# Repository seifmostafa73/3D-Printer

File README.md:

# 3D-Printer

this is a SKR-inspired 3D printer baord 

# Technical information
v1.1
* ### LPC1769 : 120 MHZ Cortex®-M3 Mc 
include 512 kB of flash memory, 64 kB of data memory, Ethernet MAC, USB Device/Host/OTG, 8-channel DMA controller, 4 UARTs, 2 CAN channels, 3 SSP/SPI, 3 I2C, I2S, 8-channel 12-bit ADC, 10-bit DAC, motor control PWM, Quadrature Encoder interface, 4 general purpose timers, 6-output general purpose PWM, ultra-low power Real-Time Clock with separate battery supply, and up to 70 general purpose I/O pins. The LPC1769 is pin-compatible to the 100-pin LPC2368 Arm7™ MCU 

* ### Integrated Buck-Converted - 5V output
* ### Integrated 15A heat-bed MOSFET controller
* ### 2 Controlled Fans
* ### 4 integrated TMC5160 Circuits [the circuit is desinged to be easily repolaced in case of any failure.]
* ### on-Board ESP32 for wifi support
* ### USB Port
* ### 3-Axis end stops 
* ### 3 Analog pins ready for extensions
* ### SPI pins for programming 
* ### Seperate GND, AGND planes
* ### replacable power fuses
* ### calculated Singal integrity [Cross-talk , Power Dissipation , Diffrential pairs ,Current and voltage limits , Protetion cirucits ]

# 3D preview
https://a360.co/3tKiZm6

# ScreenShots

[Motherboard V1.1.pdf](https://github.com/seifmostafa73/3D-Printer/files/8233542/Motherboard.V1.1.pdf)

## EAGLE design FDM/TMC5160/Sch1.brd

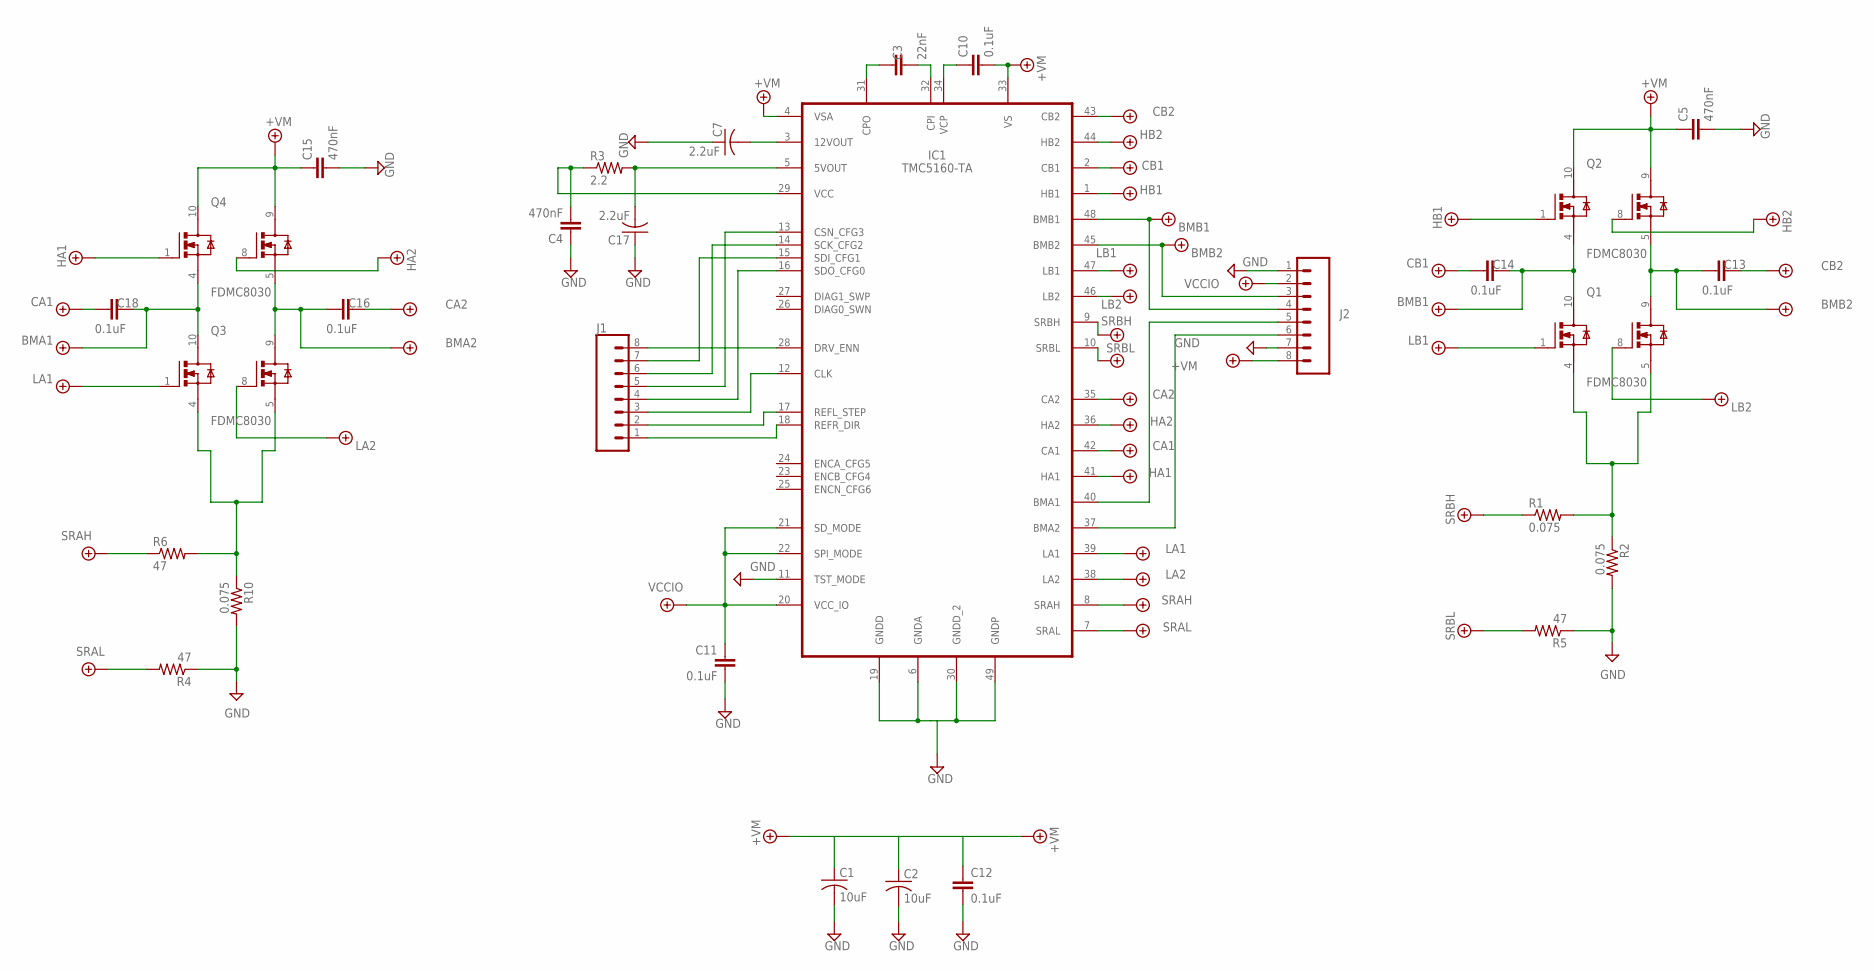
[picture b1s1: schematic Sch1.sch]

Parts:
C1, C2: 10uF; C0805
C3: 22nF; 0603
C4, C5, C15: 470nF; 0402
C7, C17: 2.2uF; C0402
C10, C11, C12, C13, C14, C16, C18: 0.1uF; 0402
IC1: TMC5160-TA; TQFP48-EP
J1, J2: CONN_08"; 1X08
Q1, Q2, Q3, Q4: FDMC8030; TRANS_FDMC8030
R1, R2, R10: 0.075; R1206
R3: 2.2; R0402
R4, R5, R6: 47; R0402

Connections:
+5V: C11.1, IC1.20 (VCC_IO), IC1.21 (SD_MODE), IC1.22 (SPI_MODE), J2.2
-4.1V: C1.1, C2.1, C5.1, C10.2, C12.1, C13.1, C13.2, C14.1, C14.2, C15.1, C16.1, C16.2, C18.1, C18.2, IC1.1 (HB1), IC1.2 (CB1), IC1.4 (VSA), IC1.7 (SRAL), IC1.8 (SRAH), IC1.9 (SRBH), IC1.10 (SRBL), IC1.33 (VS), IC1.35 (CA2), IC1.36 (HA2), IC1.38 (LA2), IC1.39 (LA1), IC1.41 (HA1), IC1.42 (CA1), IC1.43 (CB2), IC1.44 (HB2), IC1.45 (BMB2), IC1.46 (LB2), IC1.47 (LB1), IC1.48 (BMB1), J2.3, J2.4, J2.8, Q1.1 (G1), Q1.8 (G2), Q1.9 (D2), Q1.10 (D1), Q2.1 (G1), Q2.4 (S1), Q2.5 (S2), Q2.8 (G2), Q2.9 (D2), Q2.10 (D1), Q3.1 (G1), Q3.8 (G2), Q3.9 (D2), Q3.10 (D1), Q4.1 (G1), Q4.4 (S1), Q4.5 (S2), Q4.8 (G2), Q4.9 (D2), Q4.10 (D1), R1.1, R4.2, R5.2, R6.1
GND: C1.2, C2.2, C4.1, C5.2, C7.1, C11.2, C12.2, C15.2, C17.1, IC1.6 (GNDA), IC1.11 (TST_MODE), IC1.19 (GNDD), IC1.30 (GNDD_2), IC1.49 (GNDP), J2.1, J2.7, R2.2, R4.1, R5.1, R10.2
unnamed: C10.1, IC1.34 (VCP)
unnamed: IC1.18 (REFR_DIR), J1.1
unnamed: C3.1, IC1.31 (CPO)
unnamed: C3.2, IC1.32 (CPI)
unnamed: C7.2, IC1.3 (12VOUT)
unnamed: C17.2, IC1.5 (5VOUT), R3.2
unnamed: C4.2, IC1.29 (VCC), R3.1
unnamed: IC1.17 (REFL_STEP), J1.2
unnamed: IC1.12 (CLK), J1.3
unnamed: IC1.16 (SDO_CFG0), J1.4
unnamed: IC1.13 (CSN_CFG3), J1.5
unnamed: IC1.14 (SCK_CFG2), J1.6
unnamed: IC1.15 (SDI_CFG1), J1.7
unnamed: IC1.28 (DRV_ENN), J1.8
unnamed: IC1.40 (BMA1), J2.5
unnamed: IC1.37 (BMA2), J2.6
unnamed: Q3.4 (S1), Q3.5 (S2), R6.2, R10.1
unnamed: Q1.4 (S1), Q1.5 (S2), R1.2, R2.1

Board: 2 copper layers, 29 parts (0 on the bottom side), 21 nets, no tracks yet.

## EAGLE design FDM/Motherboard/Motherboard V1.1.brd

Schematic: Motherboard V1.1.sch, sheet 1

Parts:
C6, C8, C9, C22, C23, C24, C27: 22UF; C0805
C19, C21, C25, C32, C33, C34, C35, C36, C37, C38, C39, C40: 0.1UF; C0805
C20: 4700PF; C0805
C26: 10UF; C0805
C28: 220UF; E5-10,5
C29, C31: 100nF; C0805
C30: 200UF; E5-10,5
C41, C42: 18PF; C0805
C44, C45, C59, C60, C61, C75, C76, C77, C91, C92, C93, C107: 10uF; C0805
C46, C62, C78, C94: 22nF; 0603
C47, C55, C58, C63, C71, C74, C79, C87, C90, C95, C103, C106: 470nF; 0402
C48, C54, C64, C70, C80, C86, C96, C102: 2.2uF; C0402
C49, C50, C51, C52, C53, C56, C57, C65, C66, C67, C68, C69, C72, C73, C81, C82, C83, C84, C85, C88, C89, C97, C98, C99, C100, C101, C104, C105: 0.1uF; 0402
CONTROLLED-FANS: PINHD-2X2; 2X02
D1: DIODE-DO214AA; DO214AA
D2: PD3S160; POWERDI323
EXP1, EXP2: 2510-; PAK100/2500-10
EXPANSION3: MA06-2
EXTRA1, EXTRA2, EXTRA3: MA03-1
F1: 20A; SHK20Q
F2: 10A; SHK20Q
F3: 7.5A; SHK20Q
FANS: PINHD-2X2; 2X02
HEATBED: W237-102
HOTEND: W237-04P; W237-4P
IC2: LM1117MP-3.3; SOT223
IC3: LM2596S; TO263-5
IC4, IC5, IC6, IC7: TMC5160-TA; TQFP48-EP
JP1: PINHD-1X2; 1X02
JP2: swd; 1X05
L1: SRR1260-331K; INDP125125X600N
L2, L3, L4: FB-M1331; M1331
LED1: TLLR4400; LED3MM
MOSFET1: IRLR8743PBFD-PAK_TO-252AA_INF-L; D-PAK_TO-252AA_INF-L
NEOPIXEL: MA03-1
POWER: W237-102
Q5: IRLML5203; MICRO3
Q6: 120MHZ; HC49/S
Q7, Q8, Q9, Q10, Q11, Q12, Q13, Q14, Q15, Q16, Q17, Q18, Q19, Q20, Q21, Q22: FDMC8030; TRANS_FDMC8030
R1, R2, R3, R37: 100; R0805
R7, R8: 27; R0805
R9: SMD-RES-VARISTOR-5V-28V(0603); R0603
R11, R12: 1.5K; R0805
R13, R14, R15, R16: 4.7K; R0805
R17: 330; R0805
R18: 10k; B64Y
R19, R20, R21, R22, R23, R24, R45, R53, R61, R69: 10k; R0805
R25: 1M; R0805
R26, R28, R30, R32, R34: 1k; R0805
R27, R29, R31, R33, R35: 10K; R0805
R38, R39, R43, R46, R47, R51, R54, R55, R59, R62, R63, R67: 47; R0402
R40, R41, R44, R48, R49, R52, R56, R57, R60, R64, R65, R68: 0.075; R1206
R42, R50, R58, R66: 2.2; R0402
RV, RV1, RV2, RV3, RV4, RV5, RV6, RV7, RV8: BOURNS_INC._CG0603MLC-3.3LEBOURNS_INC._CG0603MLC-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; BOURNS_INC._CG0603MLC-3.3LE_1
S1: 10-XX; B3F-10XX
SERVO: MA03-1
SV1: FE05-1
SV2, SV9, SV12, SV15, SV18: MA04-1
SV3: MA03-2
SV7, SV8, SV10, SV11, SV13, SV14, SV16, SV17: MA08-2
SW1, SW2: JP2E; JP2
THERMISTOR1, THERMISTOR2, THERMISTOR3: 22-23-2021
U1: LPC1768FBD100,551; LQFP100_14X14_NXP
U2: NUP2114UCMR6T1G; SOP95P275X110-6N
U3: MC74HCT125ADTR2GTSSOP14_4P50X5P10_ONS-L; TSSOP14_4P50X5P10_ONS-L
U4, U5, U6, U7: IRF3205PBF; PG-TO220-3_INF
U$1: WIRELESS-WIFI-ESP-01
X1: USB-A003
XSTOP: MA03-1
YSTOP: MA03-1
ZSTOP: MA03-1

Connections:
1A: SV17.10, SV18.2
1B: SV17.12, SV18.1
2A: SV17.8, SV18.3
2B: SV17.6, SV18.4
3.3VDC: C9.1, C27.1, EXPANSION3.11, EXPANSION3.12, F3.1A, Q5.2 (S), R11.2, R13.1, R27.2, R29.2, R31.2, R33.2, R35.2, R45.1, R53.1, R61.1, R69.1, SV8.14, SV11.14, SV14.14, SV17.14, U$1.D2 (VCC)
5V-OUT: C30.+, C31.2, L1.1, R18.A, SW1.3
+3.3V: C26.1, F3.2A, IC2.2 (OUT), IC2.4 (OUT), JP2.1, L2.1, L3.1, LED1.A, RV3.2
+5V: C6.1, C8.2, C25.1, C32.2, EXP1.10, EXPANSION3.9, EXPANSION3.10, EXTRA1.3, EXTRA2.3, EXTRA3.3, IC2.3 (IN), SV1.5, SV2.1, SW1.2, SW2.3, U3.14 (VCC), XSTOP.3, YSTOP.3, ZSTOP.3
AGND: C22.1, C23.1, C24.1, L4.2, RV.1, RV1.1, RV2.1, THERMISTOR1.2, THERMISTOR2.2, THERMISTOR3.2, U1.11 (VSSA), U1.15 (VREFN)
BMA1: C105.2, IC7.40 (BMA1), Q21.10 (D1), Q22.4 (S1), SV17.9
BMA2: C104.1, IC7.37 (BMA2), Q21.9 (D2), Q22.5 (S2), SV17.7
BMB1: C101.2, IC7.48 (BMB1), Q19.10 (D1), Q20.4 (S1), SV17.11
BMB2: C100.1, IC7.45 (BMB2), Q19.9 (D2), Q20.5 (S2), SV17.5
CA1: C105.1, IC7.42 (CA1)
CA2: C104.2, IC7.35 (CA2)
CB1: C101.1, IC7.2 (CB1)
CB2: C100.2, IC7.43 (CB2)
CRYSTAL_N: C42.2, Q6.2, R25.1, U1.23 (XTAL2)
CRYSTAL_P: C41.2, Q6.1, R25.2, U1.22 (XTAL1)
DIR: IC7.18 (REFR_DIR), SV16.1
DPIN_N: R8.1, U1.30 (P0[30]/USB_D-)
DPIN_P: R7.1, R12.1, U1.29 (P0[29]/USB_D+)
DRIVERGND: C92.2, C93.2, C95.2, C96.1, C98.2, C99.2, C102.1, C103.2, C106.1, C107.2, IC7.6 (GNDA), IC7.11 (TST_MODE), IC7.19 (GNDD), IC7.30 (GNDD_2), IC7.49 (GNDP), R62.1, R65.2, R67.1, R68.2, SV17.3, SV17.15
DRIVERVBB: C92.1, C93.1, C95.1, C97.2, C99.1, C103.1, C107.1, IC7.4 (VSA), IC7.33 (VS), Q20.9 (D2), Q20.10 (D1), Q22.9 (D2), Q22.10 (D1), SV17.1
DRIVERVSS: C98.1, IC7.20 (VCC_IO), IC7.21 (SD_MODE), IC7.22 (SPI_MODE), SV17.13
D_N: R8.2, U2.6 (I/O), X1.3
D_P: R7.2, U2.1 (I/O), X1.2
E0-DIR: SV16.2, U1.49 (P0[11]/RXD2/SCL2/MAT3[1])
E0-RX: SV16.10, U1.93 (P1[4]/ENET_TX_EN)
E0-SLP: SV16.6
E0-STP: SV16.4, U1.50 (P2[13]/!EINT3/I2STX_SDA)
ENABLE: IC7.28 (DRV_ENN), SV16.15
ESP_N: U1.85 (P4[29]/TX_MCLK/MAT2[1]/RXD3), U$1.A2 (UTXD)
ESP_P: U1.82 (P4[28]/RX_MCLK/MAT2[0]/TXD3), U$1.D1 (URXD)
EXTRA1: R32.2, U1.40 (P1[26]/MCOB1/PWM1[6]/CAP0[0])
EXTRA2: R34.2, U1.39 (P1[25]/MCOA1/MAT1[1])
FANMOSFET: U3.11 (Y4), U6.1 (G), U7.1 (G)
FANPWM: R23.1, U1.70 (P2[3]/PWM1[4]/DCD1/TRACEDATA[2]), U3.12 (A4)
GND: C6.2, C8.1, C9.2, C19.1, C20.1, C21.2, C25.2, C26.2, C27.2, C28.-, C29.2, C30.-, C32.1, C33.1, C34.1, C35.1, C36.1, C37.1, C38.1, C39.1, C40.2, C41.1, C42.1, D2.A, EXP1.9, EXP2.9, EXPANSION3.1, EXPANSION3.2, EXTRA1.2, EXTRA2.2, EXTRA3.2, FANS.2, FANS.4, IC2.1 (GND), IC3.3 (GND), IC3.5 (!ON!/OFF), JP1.1, JP2.3, L4.1, LED1.K (C), MOSFET1.3 (S), NEOPIXEL.2, POWER.2, R9.2, R17.2, R20.2, R21.2, R22.2, R23.2, RV3.1, RV4.2, RV5.2, RV6.2, RV7.2, RV8.2, S1.3, SERVO.2, SV1.4, SV2.2, SV3.2, SV3.4, SV3.6, SV8.4, SV8.16, SV11.4, SV11.16, SV14.4, SV14.16, SV17.4, SV17.16, U1.31 (VSS_2), U1.41 (VSS_3), U1.55 (VSS_4), U1.72 (VSS_5), U1.83 (VSS_6), U1.97 (VSS), U3.1 (OE1), U3.4 (OE2), U3.7 (GND), U3.10 (OE3), U3.13 (OE4), U4.2 (S), U5.2 (S), U6.2 (S), U7.2 (S), U$1.A1 (GND), X1.1, XSTOP.2, YSTOP.2, ZSTOP.2
HA1: IC7.41 (HA1), Q22.1 (G1)
HA2: IC7.36 (HA2), Q22.8 (G2)
HB1: IC7.1 (HB1), Q20.1 (G1)
HB2: IC7.44 (HB2), Q20.8 (G2)
HBMOSFET: MOSFET1.1 (G), U3.8 (Y3)
HBPWM: R20.1, U1.68 (P2[5]/PWM1[6]/DTR1/TRACEDATA[0]), U3.9 (A3)
HEMOSFET1: U3.6 (Y2), U5.1 (G)
HEMOSFET2: U3.3 (Y1), U4.1 (G)
HEPWM1: R21.1, U1.66 (P2[7]/RD2/RTS1), U3.5 (A2)
HEPWM2: R22.1, U1.69 (P2[4]/PWM1[5]/DSR1/TRACEDATA[1]), U3.2 (A1)
LA1: IC7.39 (LA1), Q21.1 (G1)
LA2: IC7.38 (LA2), Q21.8 (G2)
LB1: IC7.47 (LB1), Q19.1 (G1)
LB2: IC7.46 (LB2), Q19.8 (G2)
MISO: EXPANSION3.5, U1.77 (P0[8]/I2STX_WS/MISO1/MAT2[2])
MOSI: EXPANSION3.3, U1.76 (P0[9]/I2STX_SDA/MOSI1/MAT2[3])
MOT-EN: R3.1, R69.2, SV16.16
MOT-MISO: SV7.8, SV10.8, SV13.8, SV16.8, U1.80 (P0[5]/I2SRX_WS/TD2/CAP2[1])
MOT-MOSI: SV7.14, SV10.14, SV13.14, SV16.14, U1.86 (P1[17]/ENET_MDIO)
MOT-SCK: SV7.12, SV10.12, SV13.12, SV16.12, U1.81 (P0[4]/I2SRX_CLK/RD2/CAP2[0])
MOTORMISO: IC7.16 (SDO_CFG0), SV16.7
MOTORMOSI: IC7.15 (SDI_CFG1), SV16.13
MOTORSCK: IC7.14 (SCK_CFG2), SV16.11
unnamed: EXP1.1, U1.21 (P1[30]/VBUS/AD0[4])
unnamed: EXP1.2, U1.24 (P0[28]/SCL0/USB_SCL)
unnamed: EXP1.3, U1.32 (P1[18]/USB_UP_LED/PWM1[1]/CAP1[0])
unnamed: EXP1.4, U1.33 (P1[19]/MCOA0/!USB_PPWR/CAP1[1])
unnamed: EXP1.5, U1.34 (P1[20]/MCI0/PWM1[2]/SCK0)
unnamed: EXP1.6, U1.35 (P1[21]/!MCABORT/PWM1[3]/SSEL0)
unnamed: EXP1.7, U1.36 (P1[22]/MCOB0/USB_PWRD/MAT1[0])
unnamed: EXP1.8, U1.37 (P1[23]/MCI1/PWM1[4]/MISO0)
unnamed: R1.2, U1.65 (P2[8]/TD2/TXD2)
unnamed: R2.2, U1.57 (P0[21]/RI1/RD1)
unnamed: EXP2.1, U1.61 (P0[17]/CTS1/MISO0/MISO)
unnamed: EXP2.2, U1.62 (P0[15]/TXD1/SCK0/SCK)
unnamed: EXP2.3, U1.26 (P3[26]/STCLK/MAT0[1]/PWM1[3])
unnamed: EXP2.4, U1.63 (P0[16]/RXD1/SSEL0/SSEL)
unnamed: EXP2.5, U1.27 (P3[25]/MAT0[0]/PWM1[2])
unnamed: EXP2.6, U1.60 (P0[18]/DCD1/MOSI0/MOSI)
unnamed: EXP2.7, U1.20 (P1[31]/SCK1/AD0[5])
unnamed: R3.2, U1.51 (P2[12]/!EINT2/I2STX_WS)
unnamed: R37.2, U1.74 (P2[1]/PWM1[2]/RXD1)
unnamed: C49.1, IC4.34 (VCP)
unnamed: C46.1, IC4.31 (CPO)
unnamed: C46.2, IC4.32 (CPI)
unnamed: C48.2, IC4.3 (12VOUT)
unnamed: C54.2, IC4.5 (5VOUT), R42.2
unnamed: C58.2, IC4.29 (VCC), R42.1
unnamed: Q7.4 (S1), Q7.5 (S2), R40.2, R41.1
unnamed: Q9.4 (S1), Q9.5 (S2), R39.2, R44.1
unnamed: C65.1, IC5.34 (VCP)
unnamed: C20.2, U2.2 (VN)
unnamed: HEATBED.1, MOSFET1.2 (D)
unnamed: Q5.3 (D), R12.2
unnamed: C31.1, IC3.4 (FB), R17.1, R18.S
unnamed: C28.+, C29.1, D1.C, IC3.1 (VIN)
unnamed: D2.C, IC3.2 (OUT), L1.2
unnamed: CONTROLLED-FANS.4, U6.3 (D)
unnamed: HOTEND.4, U4.3 (D)
unnamed: HOTEND.2, U5.3 (D)
unnamed: CONTROLLED-FANS.2, U7.3 (D)
unnamed: R19.1, U1.14 (!RSTOUT)
unnamed: R24.1, U1.16 (RTCX1)
unnamed: C62.1, IC5.31 (CPO)
unnamed: C62.2, IC5.32 (CPI)
unnamed: C64.2, IC5.3 (12VOUT)
unnamed: C70.2, IC5.5 (5VOUT), R50.2
unnamed: C74.2, IC5.29 (VCC), R50.1
unnamed: R26.1, R27.1, RV4.1, XSTOP.1
unnamed: EXTRA1.1, R32.1, R33.1, RV7.1
unnamed: Q11.4 (S1), Q11.5 (S2), R48.2, R49.1
unnamed: Q13.4 (S1), Q13.5 (S2), R47.2, R52.1
unnamed: R28.1, R29.1, RV5.1, YSTOP.1
unnamed: R30.1, R31.1, RV6.1, ZSTOP.1
unnamed: C81.1, IC6.34 (VCP)
unnamed: C78.1, IC6.31 (CPO)
unnamed: C78.2, IC6.32 (CPI)
unnamed: C80.2, IC6.3 (12VOUT)
unnamed: EXTRA2.1, R34.1, R35.1, RV8.1
unnamed: C86.2, IC6.5 (5VOUT), R58.2
unnamed: C90.2, IC6.29 (VCC), R58.1
unnamed: Q15.4 (S1), Q15.5 (S2), R56.2, R57.1
unnamed: Q17.4 (S1), Q17.5 (S2), R55.2, R60.1
unnamed: C97.1, IC7.34 (VCP)
unnamed: C94.1, IC7.31 (CPO)
unnamed: C94.2, IC7.32 (CPI)
unnamed: C96.2, IC7.3 (12VOUT)
unnamed: C102.2, IC7.5 (5VOUT), R66.2
unnamed: C106.2, IC7.29 (VCC), R66.1
unnamed: Q19.4 (S1), Q19.5 (S2), R64.2, R65.1
unnamed: Q21.4 (S1), Q21.5 (S2), R63.2, R68.1
NPOWER: NEOPIXEL.3, SERVO.3, SW2.2
P0.26: EXPANSION3.7, U1.6 (P0[26]/AD0[3]/AOUT/RXD3)
P0.27: EXPANSION3.8, U1.25 (P0[27]/SDA0/USB_SDA)
P38: NEOPIXEL.1, U1.38 (P1[24]/MCI2/PWM1[5]/MOSI0)
POWERIN: F1.1A, F2.2A, POWER.1
PROBE: EXTRA3.1, U1.48 (P0[10]/TXD2/SDA2/MAT3[0])
RESET: C21.1, EXP2.8, R13.2, S1.1 (S), SV1.1, U1.17 (!RESET)
RX: IC7.13 (CSN_CFG3), SV16.9
RX0: SV1.2, U1.99 (P0[3]/RXD0/AD0[6])
SCK: EXPANSION3.6, U1.78 (P0[7]/I2STX_CLK/SCK1/MAT2[1])
SCL1: SV2.4, U1.47 (P0[1]/TD1/RXD3/SCL1)
SDA1: SV2.3, U1.46 (P0[0]/RD1/TXD3/SDA1)
SERVO: SERVO.1, U1.75 (P2[0]/PWM1[1]/TXD1)
SLP: IC7.12 (CLK), SV16.5
SOFTCONNECT: Q5.1 (G), R11.1, U1.64 (P2[9]/USB_CONNECT/RXD2)
SRAH: IC7.8 (SRAH), R63.1
SRAL: IC7.7 (SRAL), R67.2
SRBH: IC7.9 (SRBH), R64.1
SRBL: IC7.10 (SRBL), R62.2
SSEL: EXPANSION3.4, U1.79 (P0[6]/I2SRX_SDA/SSEL1/MAT2[0])
STP: IC7.17 (REFL_STEP), SV16.3
SWDCLK: JP2.4, U1.5 (TCK/SWDCLK)
SWDIO: JP2.2, U1.3 (TMS/SWDIO)
TH1: C22.2, R14.2, RV.2, THERMISTOR1.1, U1.9 (P0[23]/AD0[0]/I2SRX_CLK/CAP3[0])
TH2: C23.2, R15.2, RV1.2, THERMISTOR2.1, U1.8 (P0[24]/AD0[1]/I2SRX_WS/CAP3[1])
THB: C24.2, R16.2, RV2.2, THERMISTOR3.1, U1.7 (P0[25]/AD0[2]/I2SRX_SDA/TXD3)
TRST: JP2.5, U1.4 (!TRST)
TX0: SV1.3, U1.98 (P0[2]/TXD0/AD0[7])
UC3.3V: C33.2, C34.2, C35.2, C36.2, C37.2, C38.2, C39.2, L2.2, R19.2, R24.2, U1.19 (VBAT), U1.28 (VDD(3V3)_2), U1.42 (VDD(REG)(3V3)_2), U1.54 (VDD(3V3)_3), U1.71 (VDD(3V3)_4), U1.84 (VDD(REG)(3V3)), U1.96 (VDD(3V3))
USB5V: C19.2, R9.1, SW1.1, U2.5 (VP), X1.4
VBB: CONTROLLED-FANS.1, CONTROLLED-FANS.3, D1.A, F2.1A, FANS.1, FANS.3, HOTEND.1, HOTEND.3, SV3.1, SV3.3, SV3.5, SV8.2, SV11.2, SV14.2, SV17.2
VDDA: C40.1, L3.2, R14.1, R15.1, R16.1, U1.10 (VDDA), U1.12 (VREFP)
VHEAT: F1.2A, HEATBED.2
VOT: JP1.2, SW2.1
X1A: SV8.10, SV9.2
X1B: SV8.12, SV9.1
X2A: SV8.8, SV9.3
X2B: SV8.6, SV9.4
X-DIR: SV7.2, U1.67 (P2[6]/PCAP1[0]/RI1/TRACECLK)
X-MOT-EN: R37.1, R45.2, SV7.16
X-RX: SV7.10, U1.90 (P1[10]/ENET_RXD1)
X-SLP: SV7.6
X-STP: SV7.4, U1.73 (P2[2]/PWM1[3]/CTS1/TRACEDATA[3])
XBMA1: C57.2, IC4.40 (BMA1), Q9.10 (D1), Q10.4 (S1), SV8.9
XBMA2: C56.1, IC4.37 (BMA2), Q9.9 (D2), Q10.5 (S2), SV8.7
XBMB1: C53.2, IC4.48 (BMB1), Q7.10 (D1), Q8.4 (S1), SV8.11
XBMB2: C52.1, IC4.45 (BMB2), Q7.9 (D2), Q8.5 (S2), SV8.5
XCA1: C57.1, IC4.42 (CA1)
XCA2: C56.2, IC4.35 (CA2)
XCB1: C53.1, IC4.2 (CB1)
XCB2: C52.2, IC4.43 (CB2)
XDIR: IC4.18 (REFR_DIR), SV7.1
XDRIVERGND: C44.2, C45.2, C47.2, C48.1, C50.2, C51.2, C54.1, C55.2, C58.1, C59.2, IC4.6 (GNDA), IC4.11 (TST_MODE), IC4.19 (GNDD), IC4.30 (GNDD_2), IC4.49 (GNDP), R38.1, R41.2, R43.1, R44.2, SV8.3, SV8.15
XDRIVERVBB: C44.1, C45.1, C47.1, C49.2, C51.1, C55.1, C59.1, IC4.4 (VSA), IC4.33 (VS), Q8.9 (D2), Q8.10 (D1), Q10.9 (D2), Q10.10 (D1), SV8.1
XDRIVERVSS: C50.1, IC4.20 (VCC_IO), IC4.21 (SD_MODE), IC4.22 (SPI_MODE), SV8.13
XENABLE: IC4.28 (DRV_ENN), SV7.15
XHA1: IC4.41 (HA1), Q10.1 (G1)
XHA2: IC4.36 (HA2), Q10.8 (G2)
XHB1: IC4.1 (HB1), Q8.1 (G1)
XHB2: IC4.44 (HB2), Q8.8 (G2)
XLA1: IC4.39 (LA1), Q9.1 (G1)
XLA2: IC4.38 (LA2), Q9.8 (G2)
XLB1: IC4.47 (LB1), Q7.1 (G1)
XLB2: IC4.46 (LB2), Q7.8 (G2)
XMIN: R26.2, U1.45 (P1[29]/MCOB2/PCAP1[1]/MAT0[1])
XMOTORMISO: IC4.16 (SDO_CFG0), SV7.7
XMOTORMOSI: IC4.15 (SDI_CFG1), SV7.13
XMOTORSCK: IC4.14 (SCK_CFG2), SV7.11
XRX: IC4.13 (CSN_CFG3), SV7.9
XSLP: IC4.12 (CLK), SV7.5
XSRAH: IC4.8 (SRAH), R39.1
XSRAL: IC4.7 (SRAL), R43.2
XSRBH: IC4.9 (SRBH), R40.1
XSRBL: IC4.10 (SRBL), R38.2
XSTP: IC4.17 (REFL_STEP), SV7.3
Y1A: SV11.10, SV12.2
Y1B: SV11.12, SV12.1
Y2A: SV11.8, SV12.3
Y2B: SV11.6, SV12.4
Y-DIR: SV10.2, U1.58 (P0[20]/DTR1/SCL1)
Y-MOT-EN: R1.1, R53.2, SV10.16
Y-RX: SV10.10, U1.91 (P1[9]/ENET_RXD0)
Y-SLP: SV10.6
Y-STP: SV10.4, U1.59 (P0[19]/DSR1/SDA1)
YBMA1: C73.2, IC5.40 (BMA1), Q13.10 (D1), Q14.4 (S1), SV11.9
YBMA2: C72.1, IC5.37 (BMA2), Q13.9 (D2), Q14.5 (S2), SV11.7
YBMB1: C69.2, IC5.48 (BMB1), Q11.10 (D1), Q12.4 (S1), SV11.11
YBMB2: C68.1, IC5.45 (BMB2), Q11.9 (D2), Q12.5 (S2), SV11.5
YCA1: C73.1, IC5.42 (CA1)
YCA2: C72.2, IC5.35 (CA2)
YCB1: C69.1, IC5.2 (CB1)
YCB2: C68.2, IC5.43 (CB2)
YDIR: IC5.18 (REFR_DIR), SV10.1
YDRIVERGND: C60.2, C61.2, C63.2, C64.1, C66.2, C67.2, C70.1, C71.2, C74.1, C75.2, IC5.6 (GNDA), IC5.11 (TST_MODE), IC5.19 (GNDD), IC5.30 (GNDD_2), IC5.49 (GNDP), R46.1, R49.2, R51.1, R52.2, SV11.3, SV11.15
YDRIVERVBB: C60.1, C61.1, C63.1, C65.2, C67.1, C71.1, C75.1, IC5.4 (VSA), IC5.33 (VS), Q12.9 (D2), Q12.10 (D1), Q14.9 (D2), Q14.10 (D1), SV11.1
YDRIVERVSS: C66.1, IC5.20 (VCC_IO), IC5.21 (SD_MODE), IC5.22 (SPI_MODE), SV11.13
YENABLE: IC5.28 (DRV_ENN), SV10.15
YHA1: IC5.41 (HA1), Q14.1 (G1)
YHA2: IC5.36 (HA2), Q14.8 (G2)
YHB1: IC5.1 (HB1), Q12.1 (G1)
YHB2: IC5.44 (HB2), Q12.8 (G2)
YLA1: IC5.39 (LA1), Q13.1 (G1)
YLA2: IC5.38 (LA2), Q13.8 (G2)
YLB1: IC5.47 (LB1), Q11.1 (G1)
YLB2: IC5.46 (LB2), Q11.8 (G2)
YMIN: R28.2, U1.44 (P1[28]/MCOA2/PCAP1[0]/MAT0[0])
YMOTORMISO: IC5.16 (SDO_CFG0), SV10.7
YMOTORMOSI: IC5.15 (SDI_CFG1), SV10.13
YMOTORSCK: IC5.14 (SCK_CFG2), SV10.11
YRX: IC5.13 (CSN_CFG3), SV10.9
YSLP: IC5.12 (CLK), SV10.5
YSRAH: IC5.8 (SRAH), R47.1
YSRAL: IC5.7 (SRAL), R51.2
YSRBH: IC5.9 (SRBH), R48.1
YSRBL: IC5.10 (SRBL), R46.2
YSTP: IC5.17 (REFL_STEP), SV10.3
Z1A: SV14.10, SV15.2
Z1B: SV14.12, SV15.1
Z2A: SV14.8, SV15.3
Z2B: SV14.6, SV15.4
Z-DIR: SV13.2, U1.52 (P2[11]/!EINT1/I2STX_CLK)
Z-MOT-EN: R2.1, R61.2, SV13.16
Z-RX: SV13.10, U1.92 (P1[8]/ENET_CRS)
Z-SLP: SV13.6
Z-STP: SV13.4, U1.56 (P0[22]/RTS1/TD1)
ZBMA1: C89.2, IC6.40 (BMA1), Q17.10 (D1), Q18.4 (S1), SV14.9
ZBMA2: C88.1, IC6.37 (BMA2), Q17.9 (D2), Q18.5 (S2), SV14.7
ZBMB1: C85.2, IC6.48 (BMB1), Q15.10 (D1), Q16.4 (S1), SV14.11
ZBMB2: C84.1, IC6.45 (BMB2), Q15.9 (D2), Q16.5 (S2), SV14.5
ZCA1: C89.1, IC6.42 (CA1)
ZCA2: C88.2, IC6.35 (CA2)
ZCB1: C85.1, IC6.2 (CB1)
ZCB2: C84.2, IC6.43 (CB2)
ZDIR: IC6.18 (REFR_DIR), SV13.1
ZDRIVERGND: C76.2, C77.2, C79.2, C80.1, C82.2, C83.2, C86.1, C87.2, C90.1, C91.2, IC6.6 (GNDA), IC6.11 (TST_MODE), IC6.19 (GNDD), IC6.30 (GNDD_2), IC6.49 (GNDP), R54.1, R57.2, R59.1, R60.2, SV14.3, SV14.15
ZDRIVERVBB: C76.1, C77.1, C79.1, C81.2, C83.1, C87.1, C91.1, IC6.4 (VSA), IC6.33 (VS), Q16.9 (D2), Q16.10 (D1), Q18.9 (D2), Q18.10 (D1), SV14.1
ZDRIVERVSS: C82.1, IC6.20 (VCC_IO), IC6.21 (SD_MODE), IC6.22 (SPI_MODE), SV14.13
ZENABLE: IC6.28 (DRV_ENN), SV13.15
ZHA1: IC6.41 (HA1), Q18.1 (G1)
ZHA2: IC6.36 (HA2), Q18.8 (G2)
ZHB1: IC6.1 (HB1), Q16.1 (G1)
ZHB2: IC6.44 (HB2), Q16.8 (G2)
ZLA1: IC6.39 (LA1), Q17.1 (G1)
ZLA2: IC6.38 (LA2), Q17.8 (G2)
ZLB1: IC6.47 (LB1), Q15.1 (G1)
ZLB2: IC6.46 (LB2), Q15.8 (G2)
ZMIN: R30.2, U1.43 (P1[27]/CLKOUT/!USB_OVRCR/CAP0[1])
ZMOTORMISO: IC6.16 (SDO_CFG0), SV13.7
ZMOTORMOSI: IC6.15 (SDI_CFG1), SV13.13
ZMOTORSCK: IC6.14 (SCK_CFG2), SV13.11
ZRX: IC6.13 (CSN_CFG3), SV13.9
ZSLP: IC6.12 (CLK), SV13.5
ZSRAH: IC6.8 (SRAH), R55.1
ZSRAL: IC6.7 (SRAL), R59.2
ZSRBH: IC6.9 (SRBH), R56.1
ZSRBL: IC6.10 (SRBL), R54.2
ZSTP: IC6.17 (REFL_STEP), SV13.3

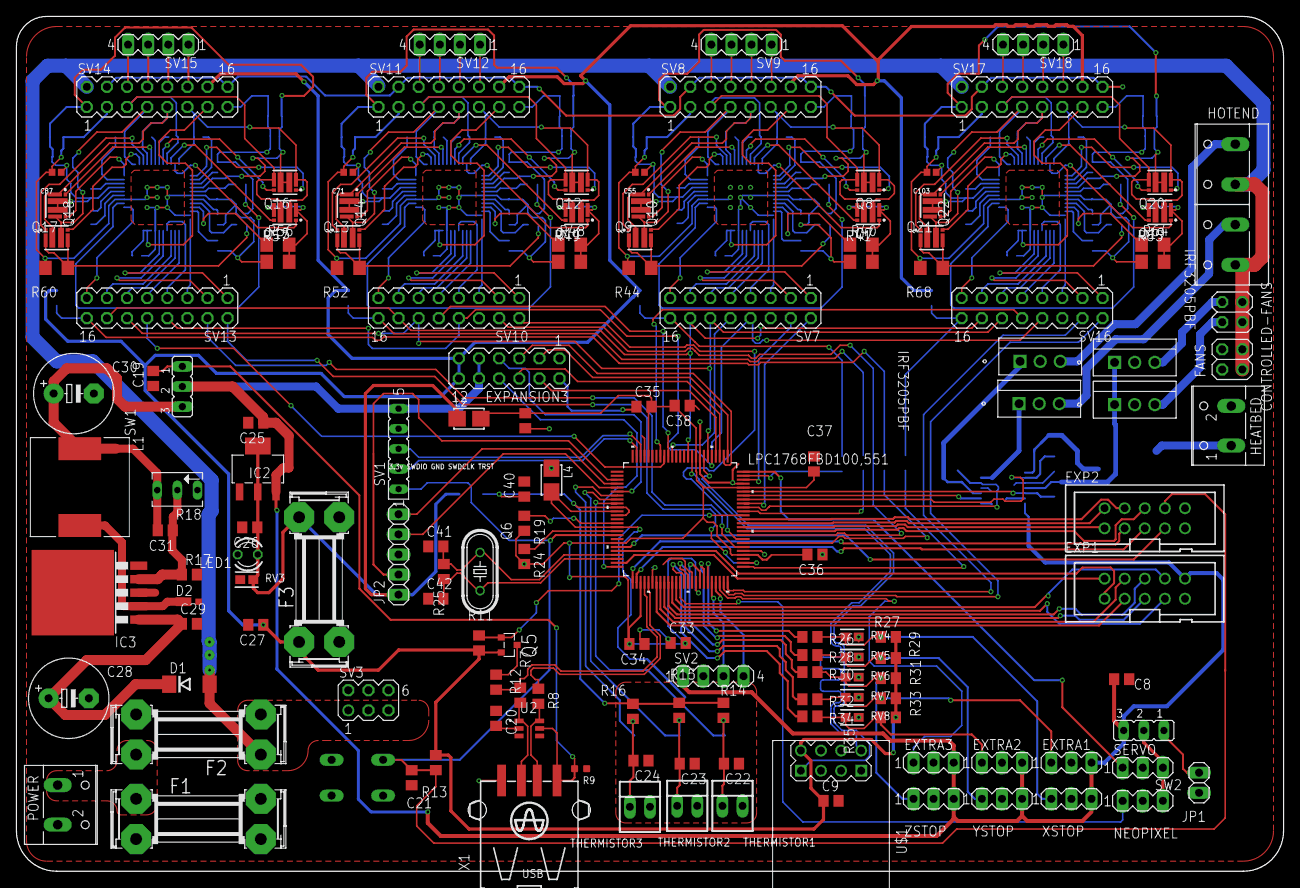
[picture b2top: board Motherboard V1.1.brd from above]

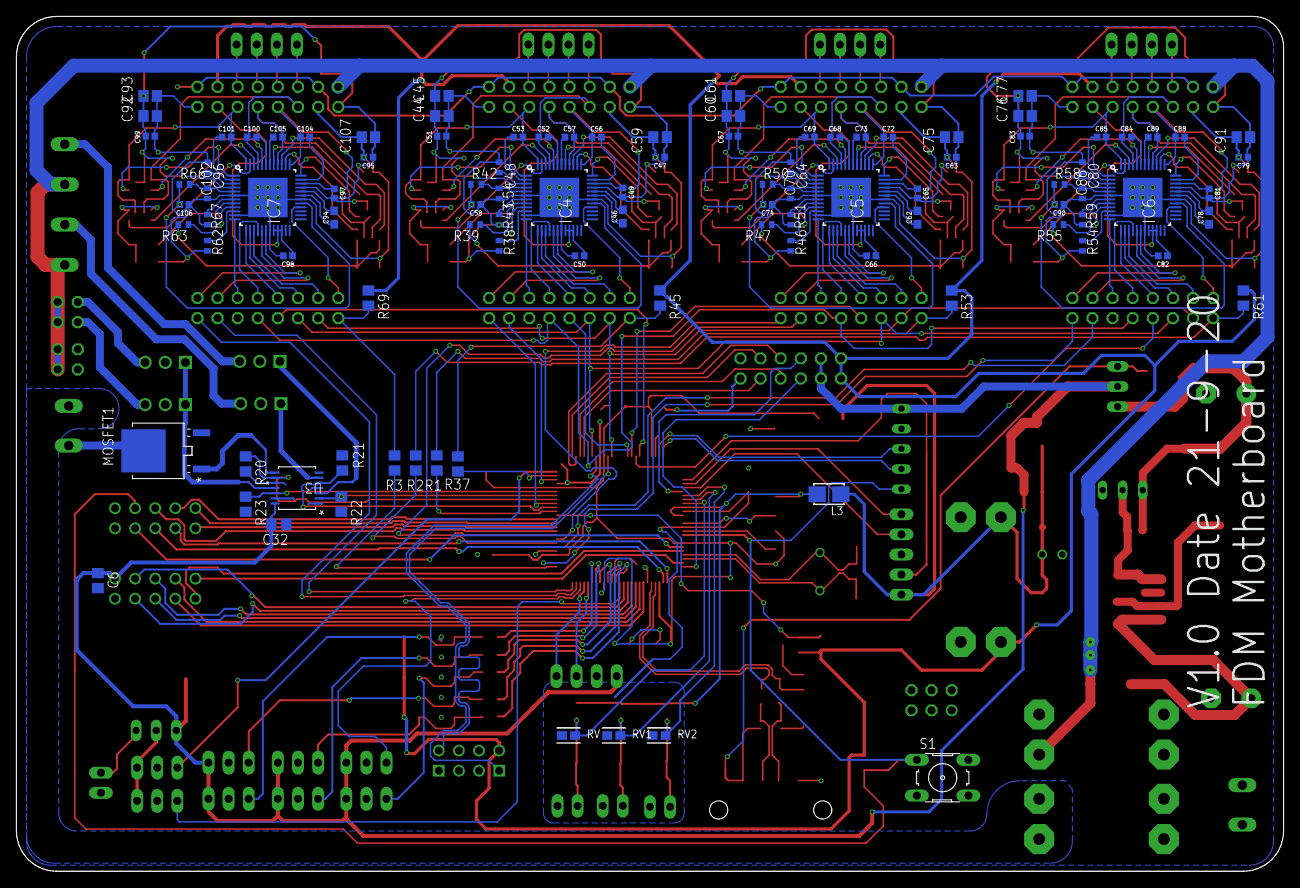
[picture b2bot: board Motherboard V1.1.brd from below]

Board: 2 copper layers, 160.0 x 108.0 mm, 247 parts (101 on the bottom side), 283 nets.

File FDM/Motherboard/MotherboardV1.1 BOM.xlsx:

Qty/BRD | Value | Device | Package | Parts | Description
1 | N/A | 10-XX | B3F-10XX | S1 | OMRON SWITCH[COULD BE SPARED FOR A REGULAR SWITCH]
1 | N/A | DIODE-DO214AA | DO214AA | D1 | DIODE
1 | N/A | FE05-1 | FE05-1 | SV1 | FEMALE HEADER
2 | N/A | JP2E | JP2 | SW1, SW2 | JUMPER
8 | N/A | MA03-1 | MA03-1 | EXTRA1, EXTRA2, EXTRA3, NEOPIXEL, SERVO, XSTOP, YSTOP, ZSTOP | PIN HEADER
1 | N/A | MA03-2 | MA03-2 | SV3 | PIN HEADER
5 | N/A | MA04-1 | MA04-1 | SV2, SV9, SV12, SV15, SV18 | PIN HEADER
1 | N/A | MA06-2 | MA06-2 | EXPANSION3 | PIN HEADER
8 | N/A | MA08-2 | MA08-2 | SV7, SV8, SV10, SV11, SV13, SV14, SV16, SV17 | PIN HEADER
1 | N/A | PINHD-1X2 | 1X02 | JP1 | PIN HEADER
2 | N/A | PINHD-2X2 | 2X02 | CONTROLLED-FANS, FANS | PIN HEADER
1 | N/A | USB-A003 | USB-A003 | X1 | USB connector
1 | N/A | W237-04P | W237-4P | HOTEND | WAGO SREW CLAMP
2 | N/A | W237-102 | W237-102 | HEATBED, POWER | WAGO SCREW CLAMP
12 | 7.4999999999999997E-2 | R-US_R1206 | R1206 | R40, R41, R44, R48, R49, R52, R56, R57, R60, R64, R65, R68 | RESISTOR, American symbol
12 | 0.1UF | C-EUC0805 | C0805 | C19, C21, C25, C32, C33, C34, C35, C36, C37, C38, C39, C40 | CAPACITOR, European symbol
28 | 0.1uF | 0.1UF-0402-16V-10% | 402 | C49, C50, C51, C52, C53, C56, C57, C65, C66, C67, C68, C69, C72, C73, C81, C82,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 | 0.1µF ceramic capacitors
2 | 1.5K | R-EU_R0805 | R0805 | R11, R12 | RESISTOR, European symbol
4 | 100 | R-EU_R0805 | R0805 | R1, R2, R3, R37 | RESISTOR, European symbol
2 | 100nF | C-EUC0805 | C0805 | C29, C31 | CAPACITOR, European symbol
1 | 10A | SHK20Q | SHK20Q | F2 | FUSE HOLDER 5 x 20 mm, SH contact, E1207 Buerklin 64G6061
5 | 10K | R-EU_R0805 | R0805 | R27, R29, R31, R33, R35 | RESISTOR, European symbol
1 | 10UF | C-EUC0805 | C0805 | C26 | CAPACITOR, European symbol
10 | 10k | R-EU_R0805 | R0805 | R19, R20, R21, R22, R23, R24, R45, R53, R61, R69 | RESISTOR, European symbol
1 | 10k | TRIM_US-B64Y | B64Y | R18 | POTENTIOMETER
12 | 10uF | C-USC0805 | C0805 | C44, C45, C59, C60, C61, C75, C76, C77, C91, C92, C93, C107 | CAPACITOR, American symbol
1 | 120MHZ | CRYSTALHC49S | HC49/S | Q6 | CRYSTAL
2 | 18PF | C-EUC0805 | C0805 | C41, C42 | CAPACITOR, European symbol
1 | 1M | R-EU_R0805 | R0805 | R25 | RESISTOR, European symbol
5 | 1k | R-EU_R0805 | R0805 | R26, R28, R30, R32, R34 | RESISTOR, European symbol
4 | 2.2000000000000002 | R-US_R0402 | R0402 | R42, R50, R58, R66 | RESISTOR, American symbol
8 | 2.2uF | C-USC0402 | C0402 | C48, C54, C64, C70, C80, C86, C96, C102 | CAPACITOR, American symbol
1 | 200UF | CPOL-USE5-10.5 | E5-10,5 | C30 | POLARIZED CAPACITOR, American symbol
1 | 20A | SHK20Q | SHK20Q | F1 | FUSE HOLDER 5 x 20 mm, SH contact, E1207 Buerklin 64G6061
3 | 22-23-2021 | 22-23-2021 | 22-23-2021 | THERMISTOR1, THERMISTOR2, THERMISTOR3 | .100" (2.54mm) Center Header - 2 Pin
1 | 220UF | CPOL-USE5-10.5 | E5-10,5 | C28 | POLARIZED CAPACITOR, American symbol
7 | 22UF | C-EUC0805 | C0805 | C6, C8, C9, C22, C23, C24, C27 | CAPACITOR, European symbol
4 | 22nF | 22NF/22,000PF-0603-50V-10% | 603 | C46, C62, C78, C94 | 0.022uF/22nF/22,000pF ceramic capacitors
2 | 2510- | 2510- | PAK100/2500-10 | EXP1, EXP2 | 3M (TM) Pak 100 4-Wall Header
2 | 27 | R-EU_R0805 | R0805 | R7, R8 | RESISTOR, European symbol
1 | 330 | R-EU_R0805 | R0805 | R17 | RESISTOR, European symbol
4 | 4.7K | R-EU_R0805 | R0805 | R13, R14, R15, R16 | RESISTOR, European symbol
12 | 47 | R-US_R0402 | R0402 | R38, R39, R43, R46, R47, R51, R54, R55, R59, R62, R63, R67 | RESISTOR, American symbol
1 | 4700PF | C-EUC0805 | C0805 | C20 | CAPACITOR, European symbol
12 | 470nF | 470NF-0402-16V-10% | 402 | C47, C55, C58, C63, C71, C74, C79, C87, C90, C95, C103, C106 | 0.47uF/470nF ceramic capacitors
1 | 7.5A | SHK20Q | SHK20Q | F3 | FUSE HOLDER 5 x 20 mm, SH contact, E1207 Buerklin 64G6061
9 | BOURNS_INC._CG0603MLC-3.3LEBOURNS_INC._CG0603MLC-3.3LE_0_1 | BOURNS_INC._CG0603MLC-3.3LEBOURNS_INC._CG0603MLC-3.3LE_0_1 | BOURNS_INC._CG0603MLC-3.3LE_1 | RV, RV1, RV2, RV3, RV4, RV5, RV6, RV7, RV8 | Varistor 1 Circuit Surface Mount, MLCV 0603 (1608 Metric)
3 | FB-M1331 | FB-M1331 | M1331 | L2, L3, L4 | FERRITE BEAD
16 | FDMC8030 | FDMC8030 | TRANS_FDMC8030 | Q7, Q8, Q9, Q10, Q11, Q12, Q13, Q14, Q15, Q16, Q17, Q18, Q19, Q20, Q21, Q22 | Dual N-Channel Power Trench® MOSFET
4 | IRF3205PBF | IRF3205PBF | PG-TO220-3_INF | U4, U5, U6, U7
1 | IRLML5203 | IRLML5203 | MICRO3 | Q5 | HEXFET P-Channel Power MOSFET
1 | IRLR8743PBFD-PAK_TO-252AA_INF-L | IRLR8743PBFD-PAK_TO-252AA_INF-L | D-PAK_TO-252AA_INF-L | MOSFET1
1 | LM1117MP-3.3 | LM1117MP-3.3 | SOT223 | IC2 | 800mA Low-Dropout Linear Regulator
1 | LM2596S | LM2596S | TO263-5 | IC3 | SIMPLE SWITCHER® Power Converter 150 kHz 3A Step-Down Voltage Regulator
1 | LPC1768FBD100,551 | LPC1768FBD100,551 | LQFP100_14X14_NXP | U1
1 | MC74HCT125ADTR2GTSSOP14_4P50X5P10_ONS-L | MC74HCT125ADTR2GTSSOP14_4P50X5P10_ONS-L | TSSOP14_4P50X5P10_ONS-L | U3
1 | NUP2114UCMR6T1G | NUP2114UCMR6T1G | SOP95P275X110-6N | U2 | Uni Directional 10 V SMD ESD Protection Transient Voltage Suppressor - TSOP-6
1 | PD3S160 | PD3S160 | POWERDI323 | D2 | 1.0A SURFACE MOUNT SCHOTTKY BARRIER RECTIFIER POWERDI ® 323
1 | SMD-RES-VARISTOR-5V-28V(0603) | SMD-RES-VARISTOR-5V-28V(0603) | R0603 | R9 | 314130003
1 | SRR1260-331K | SRR1260-331K | INDP125125X600N | L1 | Inductor Power Shielded Wirewound 33uH 20% 100KHz 27Q-Factor Ferrite 3A 60mOhm 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
1 | TLLR4400 | TLLR4400 | LED3MM | LED1 | Low Current (2mA) LED 3 mm Tinted Diffused Package color RED
4 | TMC5160-TA | TMC5160-TA | TQFP48-EP | IC4, IC5, IC6, IC7 | Universal high voltage controller for two-phase bipolar stepper motor. TQFP48-EP
1 | WIRELESS-WIFI-ESP-01 | WIRELESS-WIFI-ESP-01 | WIRELESS-WIFI-ESP-01 | U$1 | Wireless Wi-Fi ESP-01 Module based on ESP8266 chip
1 | swd | PINHD-1X5 | 1X05 | JP2 | PIN HEADER

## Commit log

2022-03-11 Libraries and custom made design blocks
2022-03-11 Uploaded mother board v1.0 and v1.1
2022-03-11 Uploaded the replaceable motor driver module
2022-04-24 Uploaded BOM for version 1.1

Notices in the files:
parts and their libraries:
ESP: Released under the Creative Commons Attribution 4.0 International License: http://creativecommons.org/licenses/by/4.0
SparkFun-Capacitors: Licensing: Creative Commons ShareAlike 4.0 International - https://creativecommons.org/licenses/by-sa/4.0
